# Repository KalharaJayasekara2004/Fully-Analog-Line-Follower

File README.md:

# Fully Analog Line Following Robot

## 📌 Overview

This project presents the design and implementation of a fully analog line following robot developed for the EE2030 module at the University of Peradeniya.

The robot operates entirely without microcontrollers and is based on analog circuitry, logic gates, and flip-flop based control logic.

---

## ⚙️ Features

- Fully analog implementation
- No microcontroller usage
- SR flip-flop based control logic
- NAND gate logic optimization
- PCB-based hardware design
- Dash-line handling capability

---

## 🔧 Components Used

- KY-033 sensors
- L293D motor driver
- SR flip-flops
- NAND gates
- N20 DC motors
- Li-ion batteries

---

## 🖼️ Project Images

### Final Robot

---

## 🎥 Demonstration Video

[Click here to watch the final demonstration](https://drive.google.com/file/d/1bMnqlzevseig7BFVXOJsCPHhtffpjha0/view?usp=sharing)

---

## 📄 Documentation

The complete project report is available in the `report` folder.

---

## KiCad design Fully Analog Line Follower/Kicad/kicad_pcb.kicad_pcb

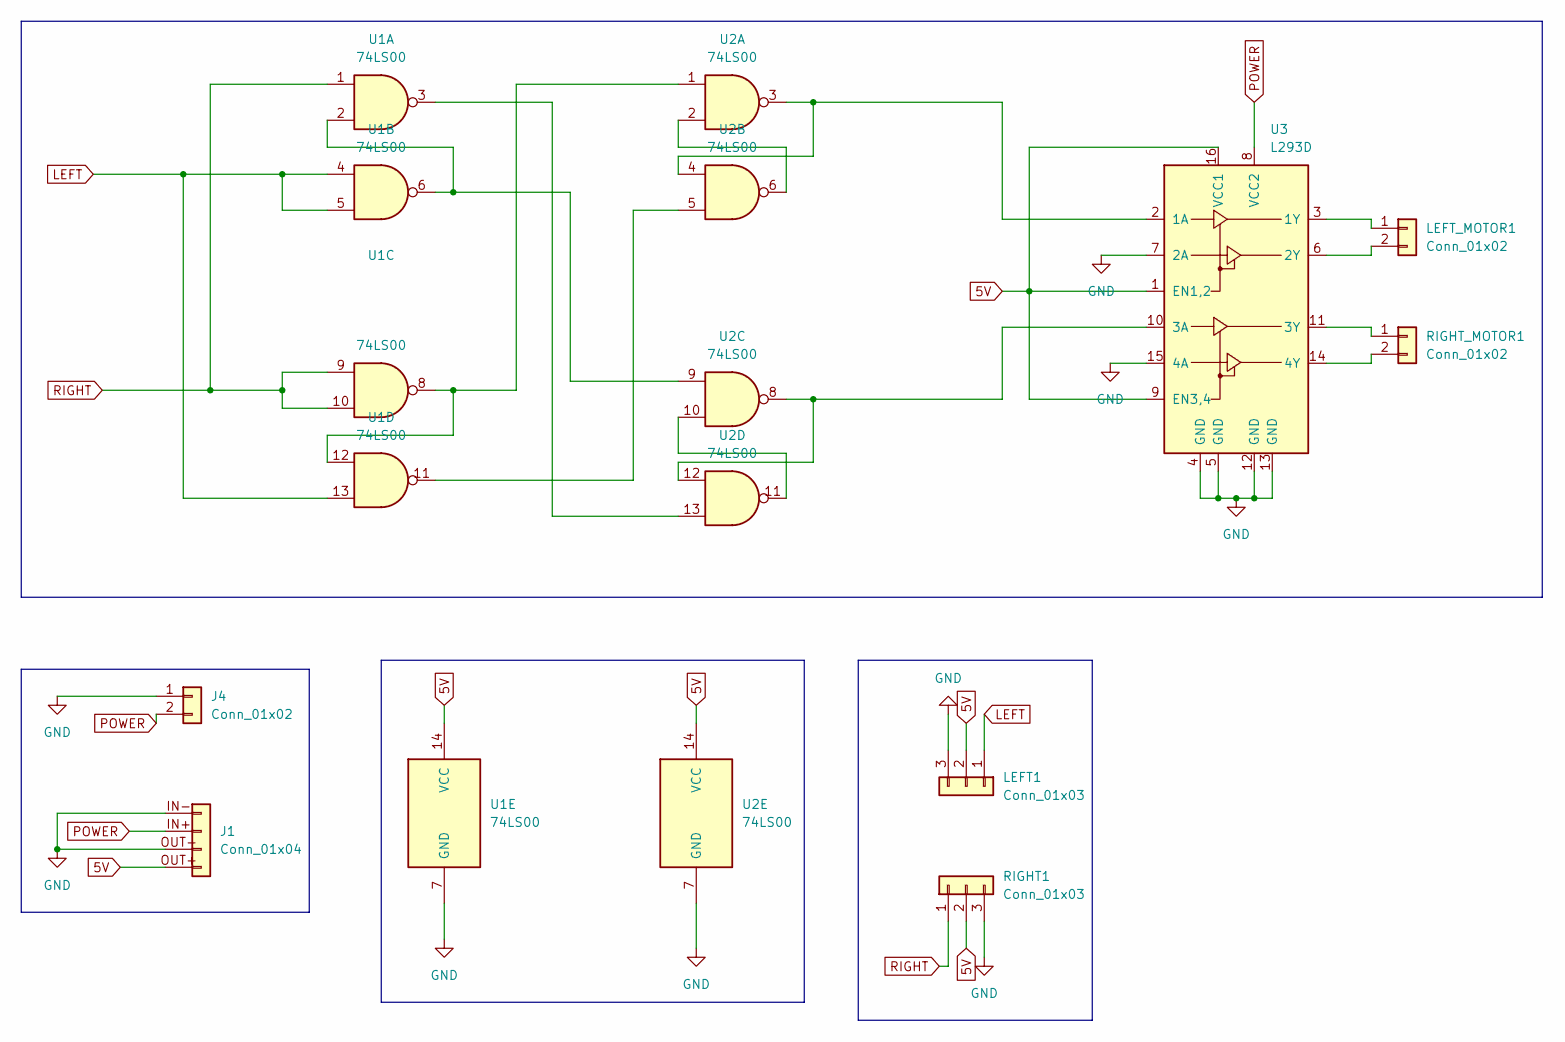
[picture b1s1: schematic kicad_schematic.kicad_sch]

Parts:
J1: Conn_01x04; LM2596
J4: Conn_01x02; PinHeader_1x02_P2.54mm_Horizontal
LEFT1: Conn_01x03; PinHeader_1x03_P2.54mm_Horizontal
LEFT_MOTOR1: Conn_01x02; PinHeader_1x02_P2.54mm_Horizontal
RIGHT1: Conn_01x03; PinHeader_1x03_P2.54mm_Horizontal
RIGHT_MOTOR1: Conn_01x02; PinHeader_1x02_P2.54mm_Horizontal
U1, U2: 74LS00; DIP-14_W7.62mm_Socket
U3: L293D; DIP-16_W7.62mm_Socket

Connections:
5V: J1.OUT+ (Pin_4), LEFT1.2, RIGHT1.2, U1.14 (VCC), U2.14 (VCC), U3.1 (EN1,2), U3.9 (EN3,4), U3.16 (VCC1)
GND: J1.IN- (Pin_1), J1.OUT- (Pin_3), J4.1, LEFT1.3, RIGHT1.3, U1.7 (GND), U2.7 (GND), U3.4 (GND), U3.5 (GND), U3.7 (2A), U3.12 (GND), U3.13 (GND), U3.15 (4A)
LEFT: LEFT1.1, U1.4, U1.5, U1.13
unnamed: LEFT_MOTOR1.1, U3.3 (1Y)
unnamed: LEFT_MOTOR1.2, U3.6 (2Y)
unnamed: RIGHT_MOTOR1.1, U3.11 (3Y)
unnamed: RIGHT_MOTOR1.2, U3.14 (4Y)
unnamed: U1.2, U1.6, U2.9
unnamed: U1.3, U2.13
unnamed: U1.11, U2.5
unnamed: U1.8, U1.12, U2.1
unnamed: U2.2, U2.6
unnamed: U2.10, U2.11
unnamed: U2.3, U2.4, U3.2 (1A)
unnamed: U2.8, U2.12, U3.10 (3A)
POWER: J1.IN+ (Pin_2), J4.2, U3.8 (VCC2)
RIGHT: RIGHT1.1, U1.1, U1.9, U1.10

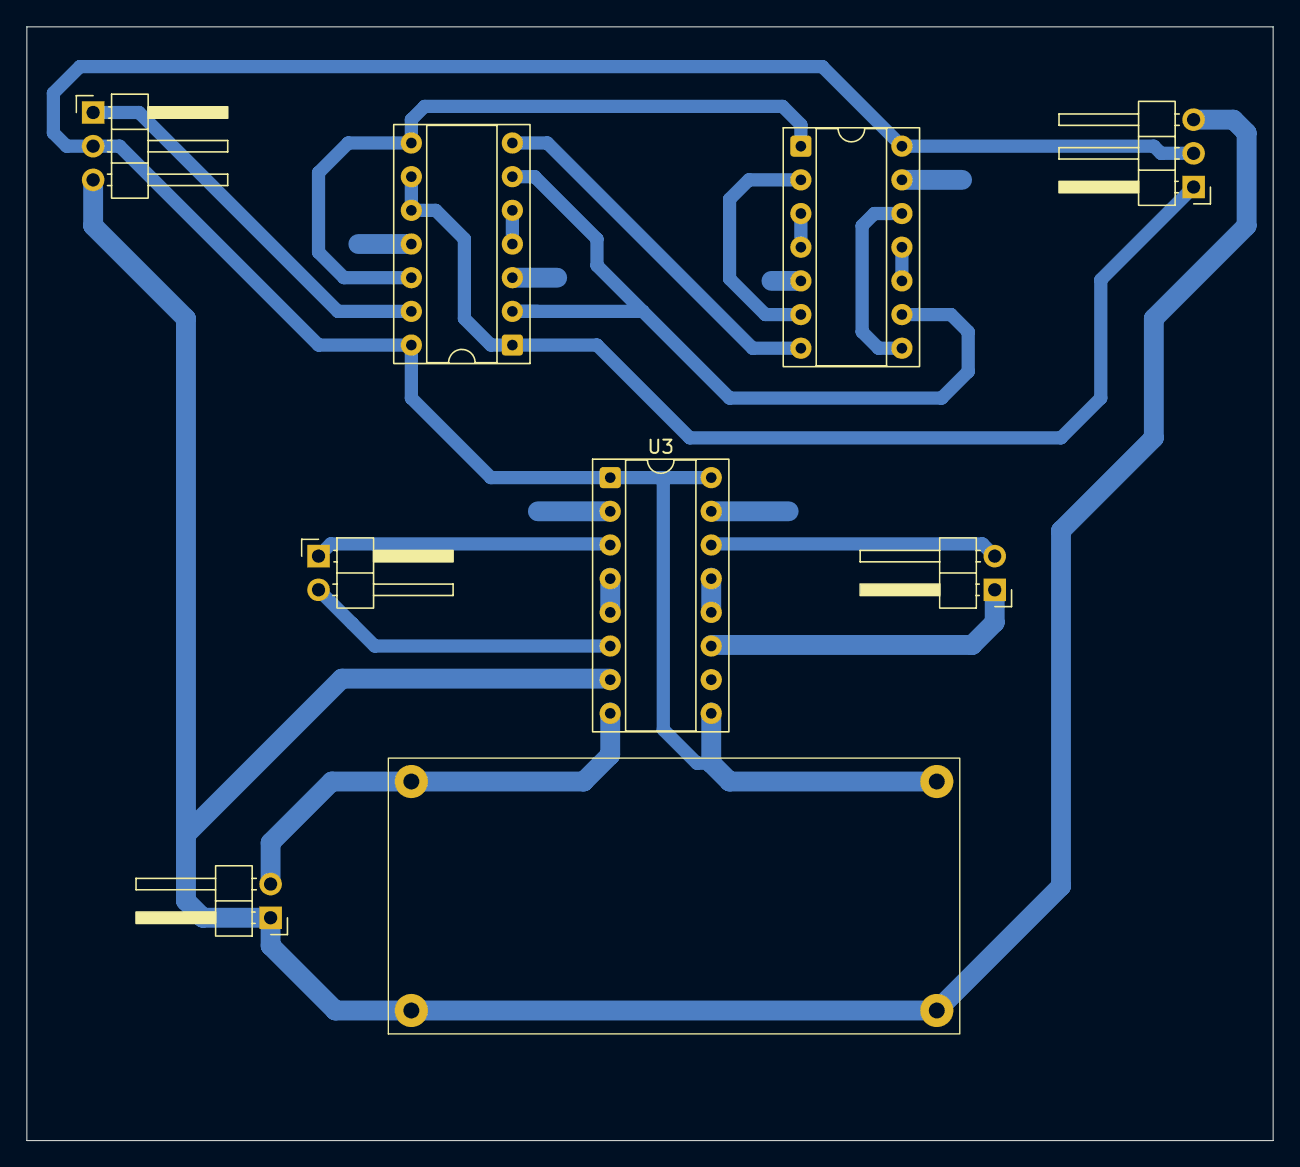
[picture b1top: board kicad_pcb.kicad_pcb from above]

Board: 2 copper layers, 94.0 x 84.0 mm, 9 parts (0 on the bottom side), 17 nets.

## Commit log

2026-05-16 Initial upload of EE2030 analog line follower project
2026-05-16 Rename Final Robot.jpg to Final_Robot.jpg
